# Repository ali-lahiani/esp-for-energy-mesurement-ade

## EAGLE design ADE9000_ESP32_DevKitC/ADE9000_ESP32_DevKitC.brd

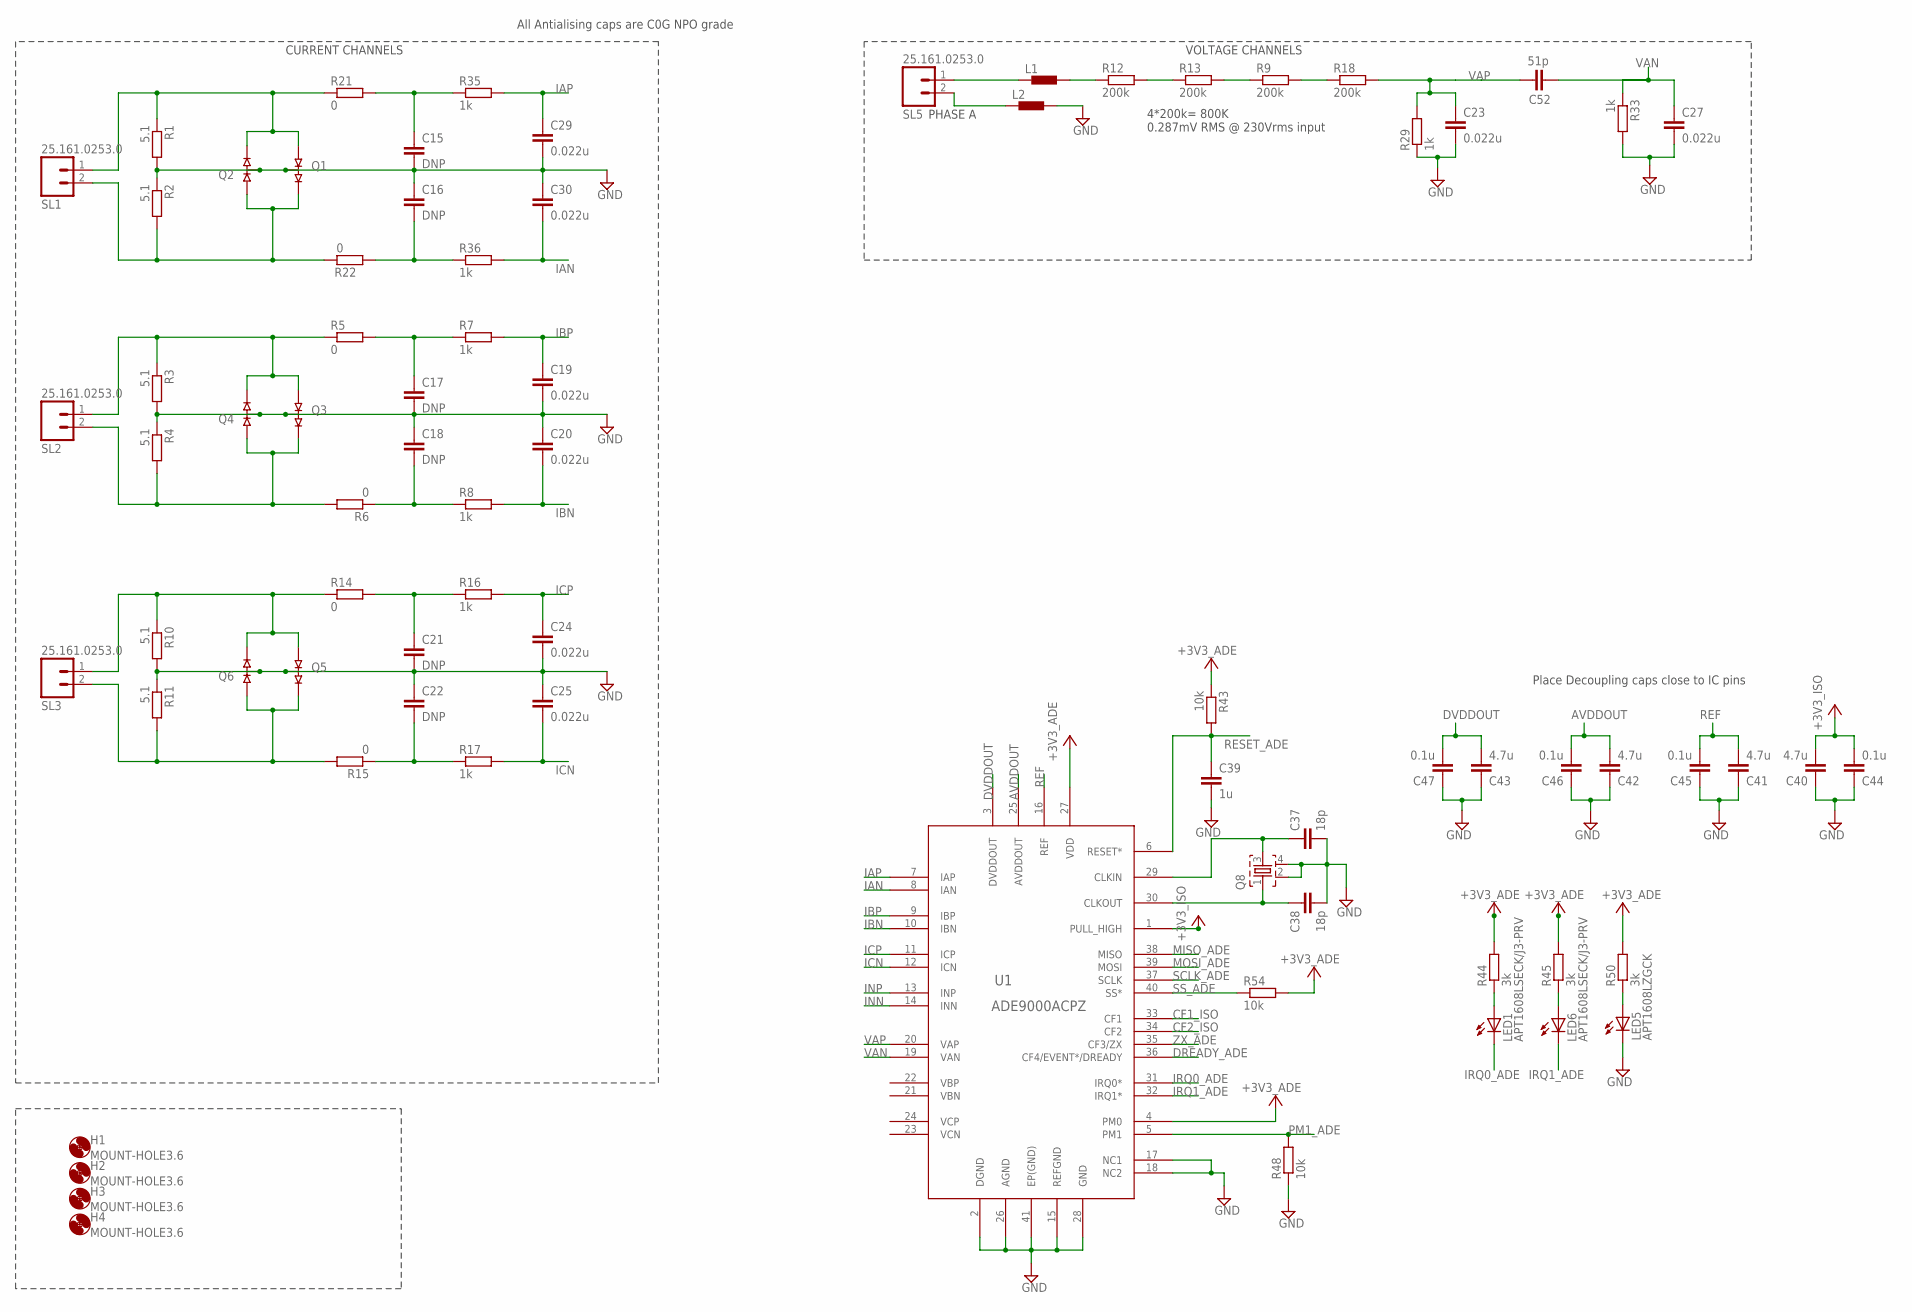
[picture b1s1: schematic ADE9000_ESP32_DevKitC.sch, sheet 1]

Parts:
C15, C16, C17, C18, C21, C22: DNP; C0805
C19, C20, C23, C24, C25, C27, C29, C30: 0.022u; C0805
C37, C38: 18p; C0402
C39: 1u; C0603
C40: 4.7u; C0805
C41, C42, C43: 4.7u; C0603
C44, C45, C46, C47: 0.1u; C0603
C52: 51p; C0402
H1, H2, H3, H4: MOUNT-HOLE3.6; 3,6
L1, L2: 1500; M0805; DIGIKEY 490-1048-1-ND
LED1, LED6: APT1608LSECK/J3-PRV; SML0603; PARTNO APT1608LSECK/J3-PRV
LED5: APT1608LZGCK; SML0603; PARTNO APT1608LZGCK
Q1, Q2, Q3, Q4, Q5, Q6: MMBD4148SE; SOT23-3; DIGIKEY MMBD4148SECT-ND
Q8: ECS-245.7-12-33Q-JES-TR; SMD_4PIN_3.2X2.1; DIGIKEY XC2178CT-ND
R1: 5.1; R0805; MFR_PART_NO_# CPF0805B5R1E1
R2, R3, R4, R10, R11: 5.1; R0805
R5, R6, R14, R15, R21, R22: 0; R0603
R7, R8, R16, R17, R29, R33, R35, R36: 1k; R0603
R9, R12, R13, R18: 200k; R2010
R43, R48, R54: 10k; R0603
R44, R45, R50: 3k; R0603
SL1, SL2, SL3, SL5: 25.161.0253.0; 02P
U1: ADE9000ACPZ; CP_40_7; DIGIKEY ADE9000ACPZ-RLCT-ND

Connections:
+3V3: C40.2, C44.2, R43.1, R44.2, R45.2, R50.2, R54.2, U1.1 (PULL_HIGH), U1.4 (PM0), U1.27 (VDD); also elsewhere on the board
AVDDOUT: C42.2, C46.2, U1.25 (AVDDOUT)
CF1_ISO: U1.33 (CF1)
CF2_ISO: U1.34 (CF2)
DREADY_ADE: U1.36 (CF4/EVENT*/DREADY); also elsewhere on the board
DVDDOUT: C43.2, C47.2, U1.3 (DVDDOUT)
GND: C15.2, C16.1, C17.2, C18.1, C19.2, C20.1, C21.2, C22.1, C23.2, C24.2, C25.1, C27.2, C29.2, C30.1, C37.2, C38.2, C39.2, C40.1, C41.1, C42.1, C43.1, C44.1, C45.1, C46.1, C47.1, L2.2, LED5.C, Q1.3, Q2.3, Q3.3, Q4.3, Q5.3, Q6.3, Q8.2, Q8.4, R1.2, R2.1, R3.2, R4.1, R10.2, R11.1, R29.1, R33.2, R48.1, U1.2 (DGND), U1.15 (REFGND), U1.17 (NC1), U1.18 (NC2), U1.26 (AGND), U1.28 (GND), U1.41 (EP(GND)); also elsewhere on the board
IAN: C30.2, R36.2, U1.8 (IAN)
IAP: C29.1, R35.2, U1.7 (IAP)
IBN: C20.2, R8.2, U1.10 (IBN)
IBP: C19.1, R7.2, U1.9 (IBP)
ICN: C25.2, R17.2, U1.12 (ICN)
ICP: C24.1, R16.2, U1.11 (ICP)
INN: U1.14 (INN)
INP: U1.13 (INP)
IRQ0_ADE: LED1.C, U1.31 (IRQ0*); also elsewhere on the board
IRQ1_ADE: LED6.C, U1.32 (IRQ1*); also elsewhere on the board
MISO_ADE: U1.38 (MISO); also elsewhere on the board
MOSI_ADE: U1.39 (MOSI); also elsewhere on the board
unnamed: C37.1, Q8.3, U1.29 (CLKIN)
unnamed: C38.1, Q8.1, U1.30 (CLKOUT)
unnamed: Q3.1, Q4.2, R3.1, R5.1, SL2.1
unnamed: Q3.2, Q4.1, R4.2, R6.2, SL2.2
unnamed: C18.2, R6.1, R8.1
unnamed: Q1.1, Q2.2, R1.1, R21.1, SL1.1
unnamed: C17.1, R5.2, R7.1
unnamed: Q5.1, Q6.2, R10.1, R14.1, SL3.1
unnamed: Q5.2, Q6.1, R11.2, R15.2, SL3.2
unnamed: C16.2, R22.1, R36.1
unnamed: L2.1, SL5.2
unnamed: C22.2, R15.1, R17.1
unnamed: C21.1, R14.2, R16.1
unnamed: LED1.A, R44.1
unnamed: LED6.A, R45.1
unnamed: L1.2, R12.1
unnamed: R12.2, R13.1
unnamed: R9.1, R13.2
unnamed: R9.2, R18.1
unnamed: Q1.2, Q2.1, R2.2, R22.2, SL1.2
unnamed: C15.1, R21.2, R35.1
unnamed: LED5.A, R50.1
unnamed: L1.1, SL5.1
PM1_ADE: R48.2, U1.5 (PM1); also elsewhere on the board
REF: C41.2, C45.2, U1.16 (REF)
RESET_ADE: C39.1, R43.2, U1.6 (RESET*); also elsewhere on the board
SCLK_ADE: U1.37 (SCLK); also elsewhere on the board
SS_ADE: R54.1, U1.40 (SS*); also elsewhere on the board
VAN: C27.1, C52.1, R33.1, U1.19 (VAN)
VAP: C23.1, C52.2, R18.2, R29.2, U1.20 (VAP)
ZX_ADE: U1.35 (CF3/ZX); also elsewhere on the board

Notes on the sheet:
Place Decoupling caps close to IC pins
VOLTAGE CHANNELS
CURRENT CHANNELS
4*200k= 800K 0.287mV RMS @ 230Vrms input
All Antialising caps are C0G NPO grade
PHASE A

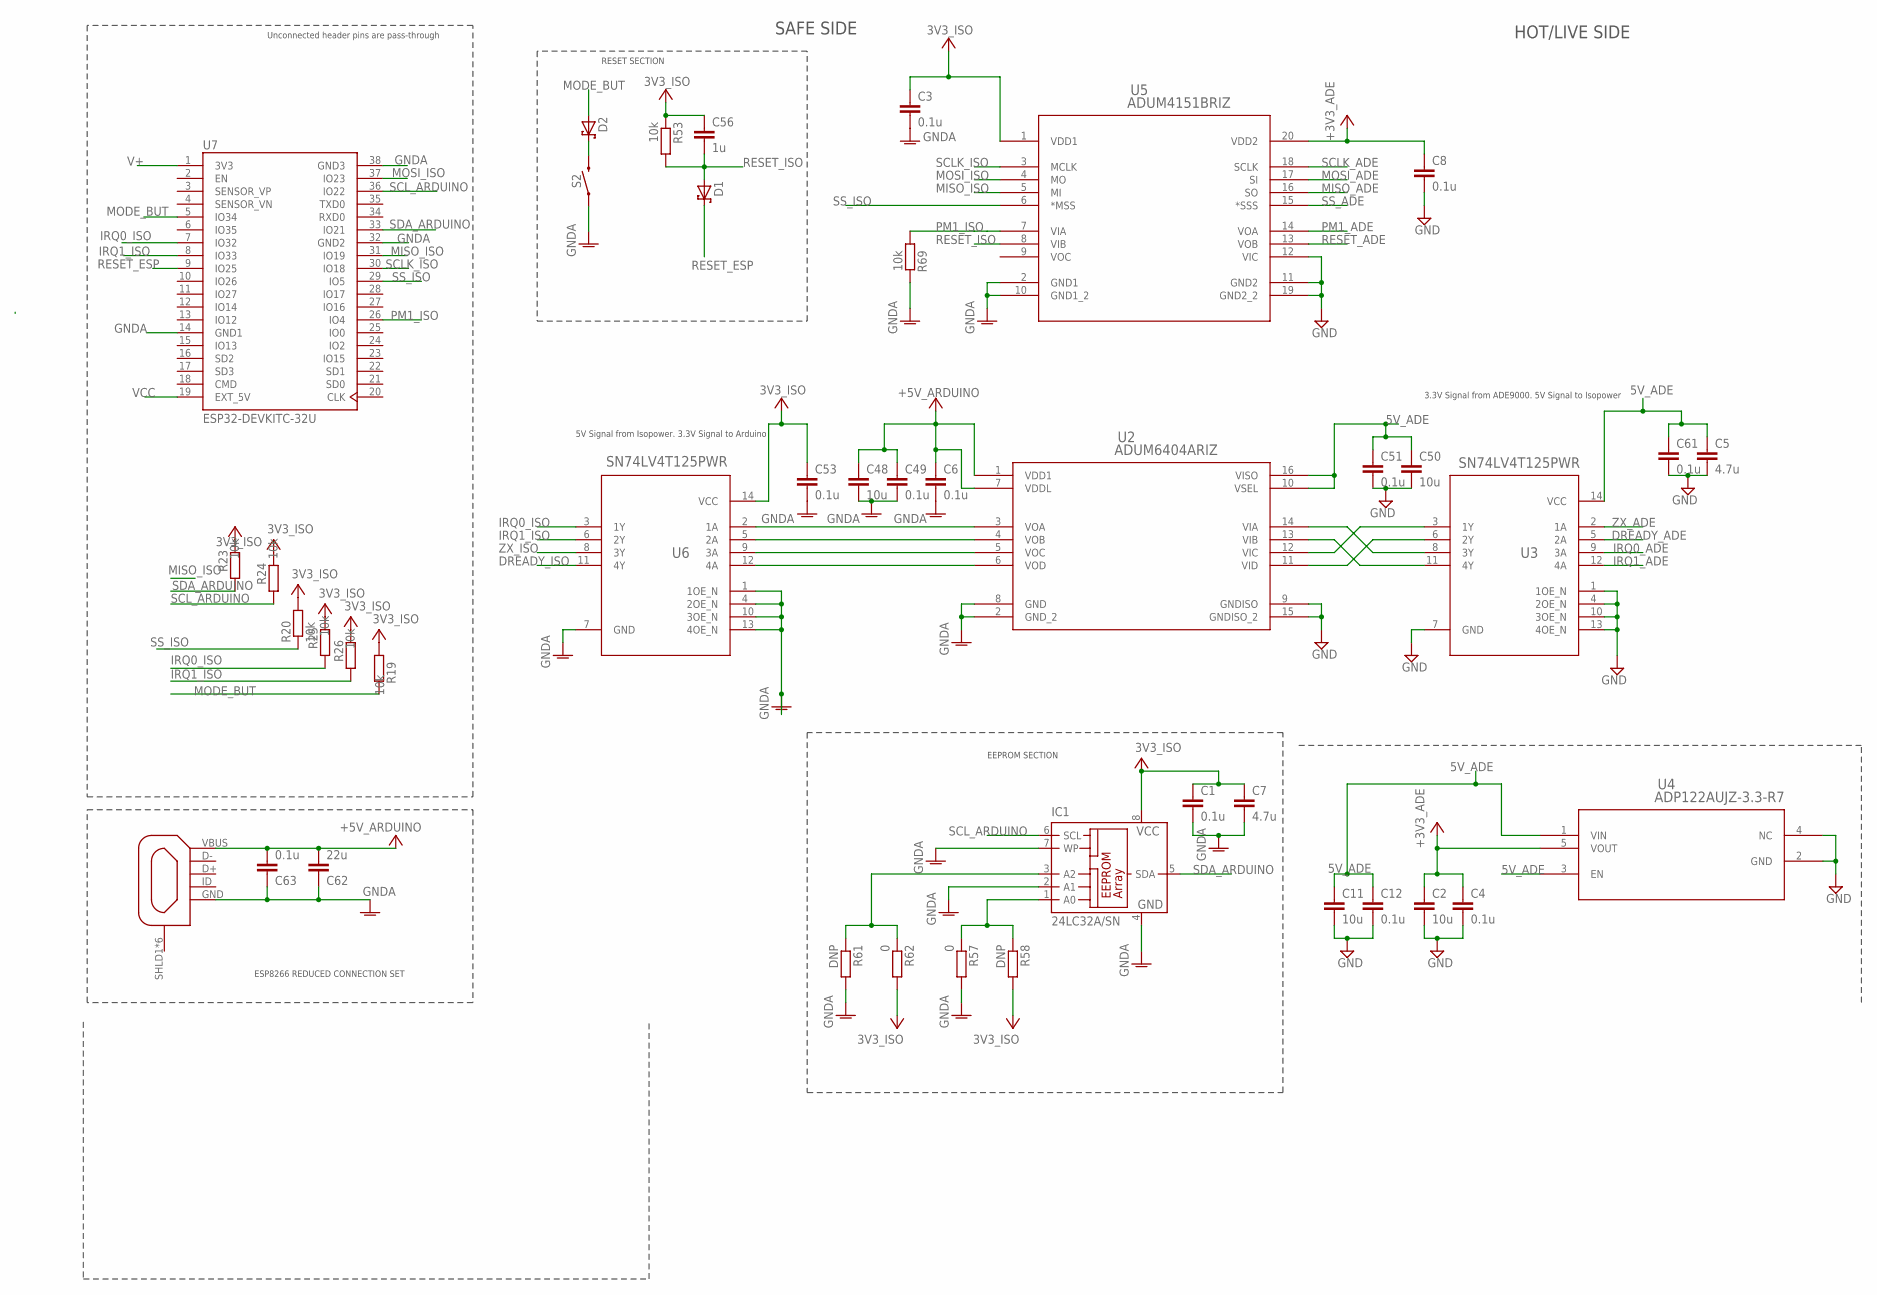
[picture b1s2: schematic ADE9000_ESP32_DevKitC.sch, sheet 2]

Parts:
C1, C3, C4, C6, C8, C12, C49, C51, C53, C61, C63: 0.1u; C0603
C2, C11, C48, C50: 10u; C0805
C5, C7: 4.7u; C0805
C56: 1u; C0603
C62: 22u; C0805
D1, D2: BAT54WS; SOD323_ST
IC1: 24LC32A/SN; SO-08
J9: ZX62-AB-5PA(31); USB-MICRO-10103594; MFRPART# ZX62-AB-5PA(31)
R19, R20, R23, R24, R25, R26, R53, R69: 10k; R0603
R57, R62: 0; R0603
R58, R61: DNP; R0603
S2: PTS645SM43SMTR92; TACTILE_SWITCH_SMD_6.2MM_TALL
U2: ADUM6404ARIZ; RI_16_1
U3, U6: SN74LV4T125PWR; PW0014A_N
U4: ADP122AUJZ-3.3-R7; UJ_5
U5: ADUM4151BRIZ; RI_20_1
U7: ESP32-DEVKITC-32U; MODULE_ESP32-DEVKITC-32U

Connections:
5V_ADE: C5.1, C11.1, C12.1, C50.1, C51.1, C61.1, U2.10 (VSEL), U2.16 (VISO), U3.14 (VCC), U4.1 (VIN), U4.3 (EN)
+3V3: C2.1, C4.1, C8.1, U4.5 (VOUT), U5.20 (VDD2); also elsewhere on the board
DREADY_ADE: U3.5 (2A); also elsewhere on the board
DREADY_ISO: U6.11 (4Y)
GND: C2.2, C4.2, C5.2, C8.2, C11.2, C12.2, C50.2, C51.2, C61.2, U2.9 (GNDISO), U2.15 (GNDISO_2), U3.1 (1OE_N), U3.4 (2OE_N), U3.7 (GND), U3.10 (3OE_N), U3.13 (4OE_N), U4.2 (GND), U4.4 (NC), U5.11 (GND2), U5.12 (VIC), U5.19 (GND2_2); also elsewhere on the board
GNDA: C1.2, C3.2, C6.2, C7.2, C48.2, C49.2, C53.2, C62.1, C63.1, IC1.2 (A1), IC1.4 (GND), IC1.7 (WP), J9.GND, R57.2, R61.2, R69.2, S2.A2 (1), U2.2 (GND_2), U2.8 (GND), U5.2 (GND1), U5.10 (GND1_2), U6.1 (1OE_N), U6.4 (2OE_N), U6.7 (GND), U6.10 (3OE_N), U6.13 (4OE_N), U7.14 (GND1), U7.32 (GND2), U7.38 (GND3)
IRQ0_ADE: U3.9 (3A); also elsewhere on the board
IRQ0_ISO: R25.1, U6.3 (1Y), U7.7 (IO32)
IRQ1_ADE: U3.12 (4A); also elsewhere on the board
IRQ1_ISO: R26.1, U6.6 (2Y), U7.8 (IO33)
MISO_ADE: U5.16 (SO); also elsewhere on the board
MISO_ISO: U5.5 (MI), U7.31 (IO19)
MODE_BUT: D2.A, R19.2, U7.5 (IO34)
MOSI_ADE: U5.17 (SI); also elsewhere on the board
MOSI_ISO: U5.4 (MO), U7.37 (IO23)
unnamed: IC1.3 (A2), R61.1, R62.1
unnamed: D2.C, S2.B2 (2)
unnamed: U2.14 (VIA), U3.8 (3Y)
unnamed: U2.13 (VIB), U3.11 (4Y)
unnamed: U2.12 (VIC), U3.3 (1Y)
unnamed: U2.11 (VID), U3.6 (2Y)
unnamed: U2.3 (VOA), U6.2 (1A)
unnamed: U2.4 (VOB), U6.5 (2A)
unnamed: U2.5 (VOC), U6.9 (3A)
unnamed: U2.6 (VOD), U6.12 (4A)
unnamed: IC1.1 (A0), R57.1, R58.1
PM1_ADE: U5.14 (VOA); also elsewhere on the board
PM1_ISO: R69.1, U5.7 (VIA), U7.26 (IO4)
RESET_ADE: U5.13 (VOB); also elsewhere on the board
RESET_ESP: D1.C, U7.9 (IO25)
RESET_ISO: C56.2, D1.A, R53.2, U5.8 (VIB)
SCLK_ADE: U5.18 (SCLK); also elsewhere on the board
SCLK_ISO: U5.3 (MCLK), U7.30 (IO18)
SCL_ARDUINO: IC1.6 (SCL), R24.1, U7.36 (IO22)
SDA_ARDUINO: IC1.5 (SDA), R23.1, U7.33 (IO21)
SS_ADE: U5.15 (*SSS); also elsewhere on the board
SS_ISO: R20.1, U5.6 (*MSS), U7.29 (IO5)
V+: C1.1, C3.1, C7.1, C53.1, C56.1, IC1.8 (VCC), R19.1, R20.2, R23.2, R24.2, R25.2, R26.2, R53.1, R58.2, R62.2, U5.1 (VDD1), U6.14 (VCC), U7.1 (3V3)
VCC: C6.1, C48.1, C49.1, C62.2, C63.2, J9.VBUS, U2.1 (VDD1), U2.7 (VDDL), U7.19 (EXT_5V)
ZX_ADE: U3.2 (1A); also elsewhere on the board
ZX_ISO: U6.8 (3Y)

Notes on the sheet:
5V Signal from Isopower. 3.3V Signal to Arduino
Unconnected header pins are pass-through
HOT/LIVE SIDE
SAFE SIDE
3.3V Signal from ADE9000. 5V Signal to Isopower
EEPROM SECTION
RESET SECTION
ESP8266 REDUCED CONNECTION SET

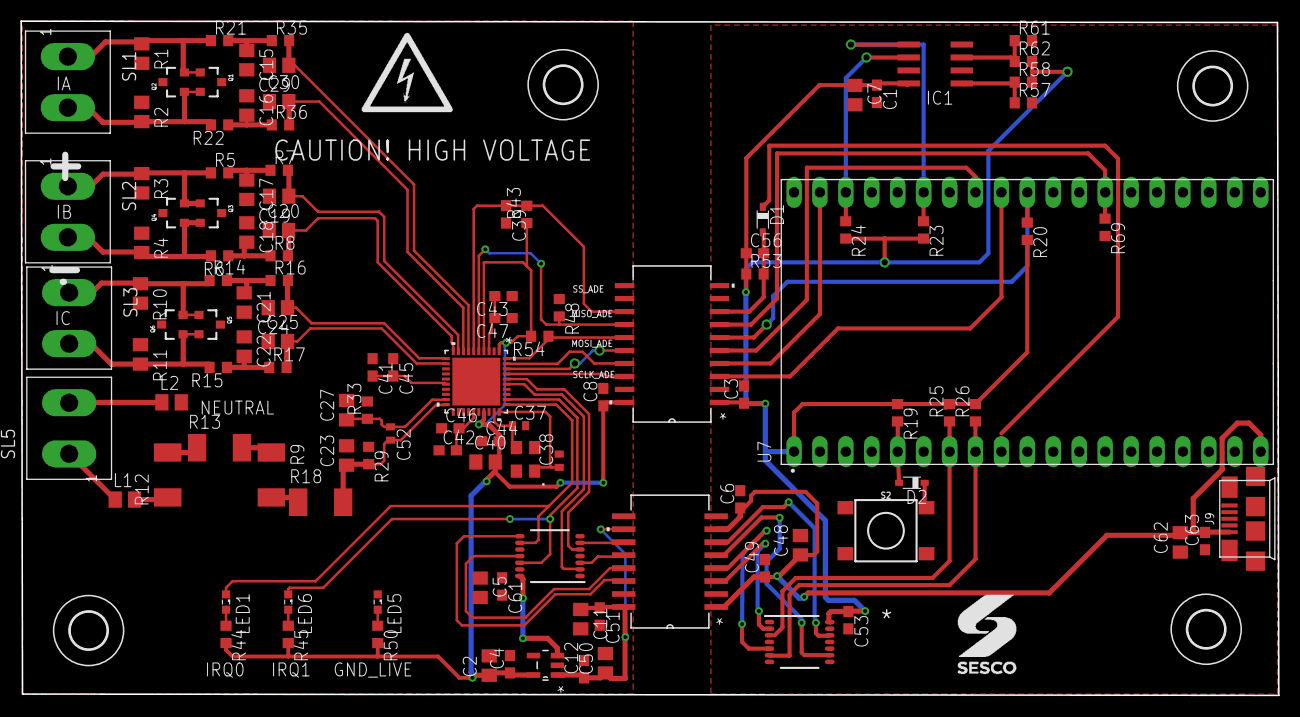
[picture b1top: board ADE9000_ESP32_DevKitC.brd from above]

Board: 2 copper layers, 123.2 x 66.0 mm, 120 parts (0 on the bottom side), 73 nets.

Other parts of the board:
DRILEGEND: DRILEGEND

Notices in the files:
parts and their libraries:
SparkFun-Switches: Licensing: Creative Commons ShareAlike 4.0 International - https://creativecommons.org/licenses/by-sa/4.0
